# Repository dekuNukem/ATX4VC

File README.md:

# ATX4VC: ATX Power on Retro Computers!

[Buy ATX4VC](https://www.tindie.com/products/dekuNukem/atx4vc-atx-power-on-retro-computers/) | [Discord](https://discord.gg/T9uuFudg7j) | [User Manual](#user-manual) | [Table of Contents](#Table-of-Contents)

ATX4VC lets you **use ATX power supply on vintage computers**.

* Plug in ATX PSU on one end
* Get 12V, 5V, 3.3V, -12V, -5V out the other!

Features:

* All common voltage rails: +12V, +5V, +3.3V, -5V, -12V.
	* Also `5V Standby` and `Power-Good`
* Toolless Lever-Actuated Terminal Block
* USB-C Power Output
* 2x PC Fan Headers

You can use ATX4VC to:

* Replace retro computer PSUs
* Test and diagnose vintage hardware
* As general-purpose multi-voltage bench PSU

## Get ATX4VC

[Click me to get one!](https://www.tindie.com/products/dekuNukem/atx4vc-atx-power-on-retro-computers/)

## PicoRC

Also [check out PicoRC](https://picorc.com) for **device-specific** and **lower-cost** PicoPSU adaptors.

## Showcase

Here ATX4VC replaces the dead PSU in my IBM 5155 Portable PC, providing +12, +5, -12, and -5V.

Note the significant simplification and space/weight saving.

It also works as a **multi-voltage bench PSU** for testing and diagnostics.

Here it powers a Macintosh Plus motherboard with +12, +5, and -12V.

## Why

Power supplies are a major failure point of old computers today.

Those early PSUs are heavy, inefficient, and (slightly) explosive! After 40 odd years, many are not working, or worse might cause damage with out-of-spec voltages.

ATX4VC is designed to replace them with much more reliable modern ATX PSUs, and help test and diagnose vintage computers.

## User Manual

### ATX vs Pico PSU

ATX4VC works with **any ATX PSU**.

Although for **permanent retrofitting**, a **PicoPSU** is recommended due to its compact size.

* [Official website](https://www.mini-box.com/DC-DC) and [distributors](https://www.mini-box.com/site/resellers.html)
    * The cheapest **80W** one should be plenty for most
    * The **160W** variant is recommended if using many expansion cards and/or **spinning hard drive**
* Avoid **generic clones**
    * They over-rate and are of low quality
* A power brick with **12V DC** and **center positive** 5.5x2.5mm barrel jack is also needed.
    * They are very popular and you might already have one
    * Make sure it has enough wattage

### Quick Start

* Don't connect any load yet!

1. Plug in ATX connector
2. On **Power Mode** switch, select **Soft Power** (left position).
3. Press the button

PSU should turn on, voltage rail LEDs should light up. 

That's the gist of it! **Please do keep reading** for more info.

### Power Modes

* Soft Power
    * **Short press** once to turn on
    * Short press again to turn off
    * Suitable for **momentary push buttons**
* Hard Power
    * **Hold down** to power on
    * **Release** to power off
    * Suitable for **latching buttons / flip switches**
    * Connected directly to ATX **PS_ON** Signal

### External Power Button and Power LED

You can also attach an **external power button** and **power LED** to the headers below:

* Note LED polarity
* LED header has built-in **330 Ohm** resistor 
* Select suitable power mode
    * Soft Power: Momentary Pushbuttons
    * Hard Power: Latching Buttons / Flip Switches

### Power Connection

* See photo for power rails
    * For aux output harness, use **8P JST VH 3.96** female connector.
* 5VSB = 5V Standby
    * Available even when PSU is off
* Power Good Signal
    * 5V when all rails are stable
    * 0V otherwise

To connect a wire:

* Strip the insulation about 12mm / 0.5in.
* Lift handle, insert, push back down.

Also, make sure the conductor is thick enough!

Label the rails, vinyl stickers are available on the [product page](https://www.tindie.com/products/dekuNukem/atx4vc-atx-power-on-retro-computers/):

### Pre-flight Checks

Before powering up:

* Double check the **correct voltage terminal** is used
* Check for **dead shorts** between each voltage rail and GND, and between themselves!

Once powered up:

* Check voltage readings on each rail

Remember that ATX4VC **DOES NOT** monitor or condition voltage rails, so ensure the PSU itself is of good quality and trustworthy!

### Current Limit

* **`5 AMPS MAX`** OVER **ANY SINGLE RAIL**
* **`7 AMPS MAX`** **TOTAL CURRENT** OVER ALL RAILS

If more is needed, **tap the power directly** from a Molex connector.

See your PSU label or datasheet to see how much current it can provide:

### Fuses

* USE FUSES RATED **5A OR LESS**
* **DO NOT BYPASS FUSES**

ATX4VC uses common **automotive fuses**.

Regular, Mini, and Low-profile Mini all work.

Simply push into the holder.

### Fan Headers

Two PC Fan headers are available. You can plug in any regular **12V PC fan**, both 3-Pin and 4-Pin.

### USB-C Power Output

An USB-C port is available for **powering external devices**.

* **OUTPUT ONLY**, **DO NOT BACKFEED** with another powered device.

## Questions or Comments?

Feel free to ask in official [Discord Chatroom](https://discord.gg/T9uuFudg7j), raise a [Github issue](https://github.com/dekuNukem/ATX4VC/issues), or email `dekunukem` `gmail.com`!

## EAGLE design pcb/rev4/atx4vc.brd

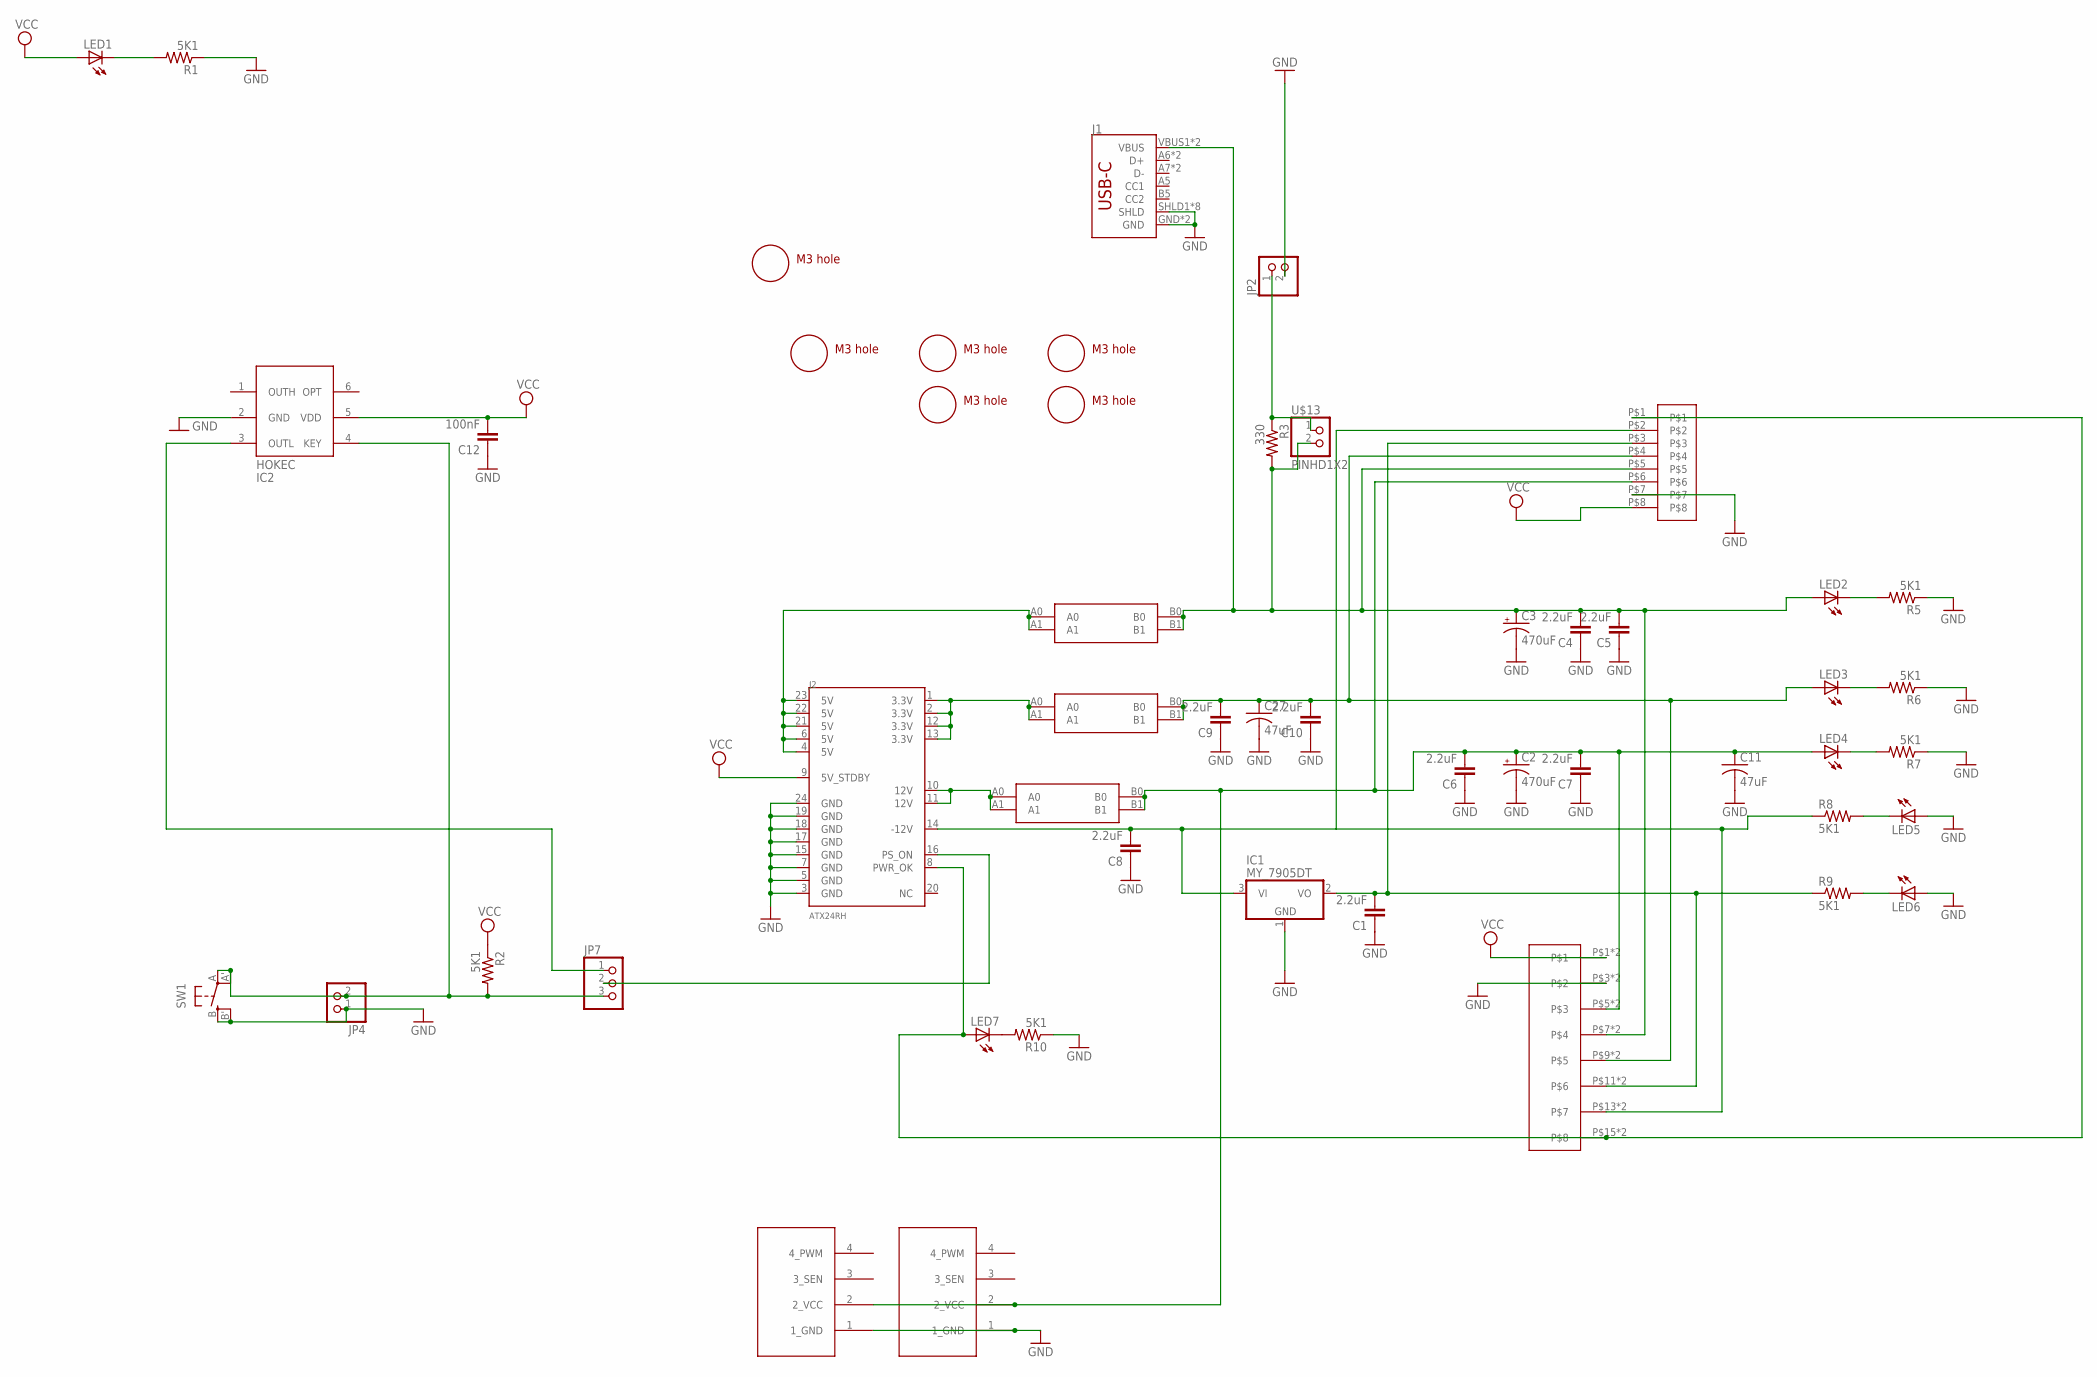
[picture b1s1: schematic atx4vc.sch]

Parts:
C1, C4, C5, C6, C7, C8, C9, C10: 2.2uF; 0805$1
C2, C3: 470uF; SMC_D
C11, C27: 47uF; C1210
C12: 100nF; 0805$1
IC1: MY_7905DT; ADAFRUIT_TO252
IC2: MAX486X/SOT; SOT23-6
J1: USB_C16PIN; USB-C-16P
J2: ATX24RH; ATX24_RIGHT_ANGLE
JP1, JP5: 4PIN_FAN; 1X04
JP2, JP4: PINHD-1X2; 1X02
JP7: PINHD-1X3CB; 1X03-CLEANBIG
LED1, LED2, LED3, LED4, LED5, LED6, LED7: LEDCHIP-LED0805; CHIP-LED0805
R1, R2, R5, R6, R7, R8, R9, R10: 5K1; 0805
R3: 330; 0805
SW1: SPST_TACT-EVQQ2; EVQ-Q2
U$1, U$2, U$3, U$4, U$5, U$6: M3_MOUNTING_HOLE; M3_MOUNTING_HOLE_PACK
U$7: 396_CONN_VH396_8P; 396_CONN_396_8P
U$9, U$10, U$11: CAR_FUSE_HOLDER3IN1; FUSE_HOLDER_3IN1
U$12: DG2204R-5.0-8DG2204-8; DG2204R-8
U$13: PINHD1X2; 1X02

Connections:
-5V: C1.2, IC1.2 (VO), R9.1, U$7.P$3, U$12.P$11, U$12.P$12
-12V: C8.2, IC1.3 (VI), J2.14 (-12V), R8.1, U$7.P$2, U$12.P$13, U$12.P$14
F3V3: C9.2, C10.2, C27.1, LED3.A, U$7.P$4, U$10.B0, U$10.B1, U$12.P$9, U$12.P$10
F5V: C3.+, C4.2, C5.2, J1.VBUS1 (VBUS), J1.VBUS2 (VBUS), LED2.A, R3.2, U$7.P$5, U$9.B0, U$9.B1, U$12.P$7, U$12.P$8, U$13.2
F12V: C2.+, C6.2, C7.2, C11.1, JP1.2 (2_VCC), JP5.2 (2_VCC), LED4.A, U$7.P$6, U$11.B0, U$11.B1, U$12.P$5, U$12.P$6
GND: C1.1, C2.-, C3.-, C4.1, C5.1, C6.1, C7.1, C8.1, C9.1, C10.1, C11.2, C12.1, C27.2, IC1.1 (GND), IC2.2 (GND), J1.GND, J1.GND2 (GND), J1.SHLD1 (SHLD), J1.SHLD2 (SHLD), J1.SHLD3 (SHLD), J1.SHLD4 (SHLD), J1.SHLD5 (SHLD), J1.SHLD6 (SHLD), J1.SHLD7 (SHLD), J1.SHLD8 (SHLD), J2.3 (GND), J2.5 (GND), J2.7 (GND), J2.15 (GND), J2.17 (GND), J2.18 (GND), J2.19 (GND), J2.24 (GND), JP1.1 (1_GND), JP2.2, JP4.1, JP5.1 (1_GND), LED5.A, LED6.A, R1.1, R5.1, R6.1, R7.1, R10.1, SW1.B (S), SW1.B' (S1), U$7.P$7, U$12.P$3, U$12.P$4
unnamed: LED7.C, R10.2
unnamed: LED6.C, R9.2
unnamed: IC2.3 (OUTL), JP7.1
unnamed: LED5.C, R8.2
unnamed: LED4.C, R7.2
unnamed: J2.4 (5V), J2.6 (5V), J2.21 (5V), J2.22 (5V), J2.23 (5V), U$9.A0, U$9.A1
unnamed: J2.8 (PWR_OK), LED7.A, U$7.P$1, U$12.P$15, U$12.P$16
unnamed: IC2.4 (KEY), JP4.2, JP7.3, R2.2, SW1.A, SW1.A' (P1)
unnamed: J2.1 (3.3V), J2.2 (3.3V), J2.12 (3.3V), J2.13 (3.3V), U$10.A0, U$10.A1
unnamed: J2.16 (PS_ON), JP7.2
unnamed: JP2.1, R3.1, U$13.1
unnamed: LED3.C, R6.2
unnamed: LED2.C, R5.2
unnamed: J2.10 (12V), J2.11 (12V), U$11.A0, U$11.A1
unnamed: LED1.C, R1.2
VCC: C12.2, IC2.5 (VDD), J2.9 (5V_STDBY), LED1.A, R2.1, U$7.P$8, U$12.P$1, U$12.P$2

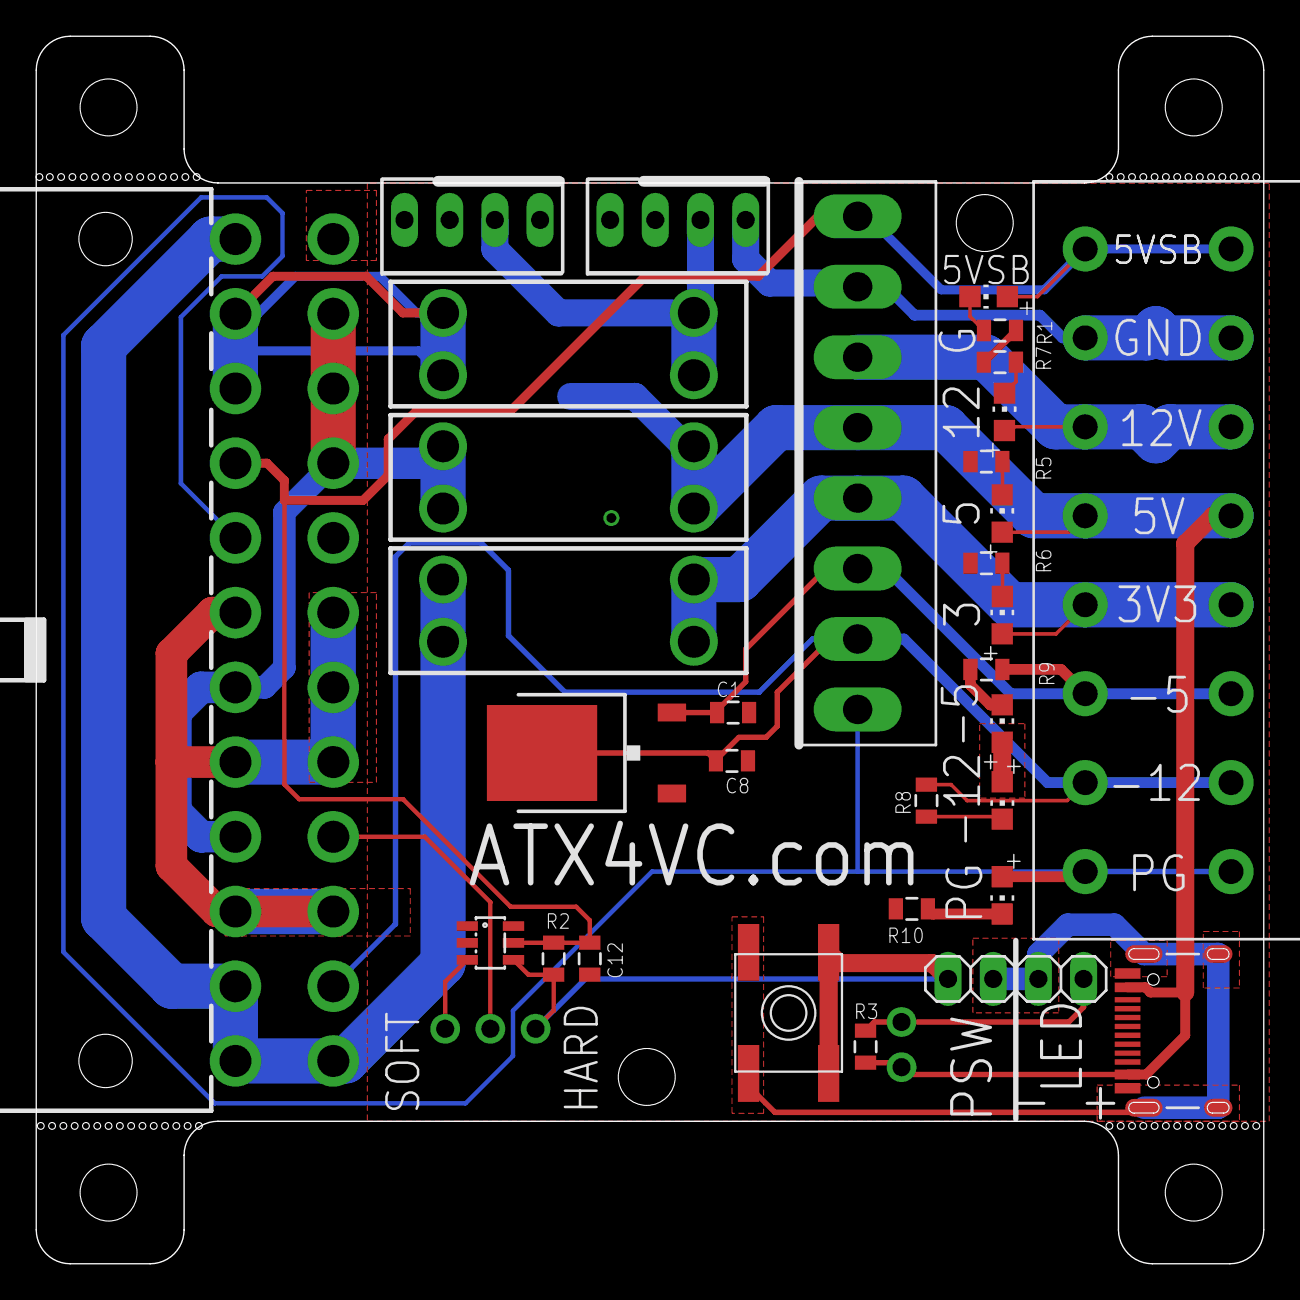
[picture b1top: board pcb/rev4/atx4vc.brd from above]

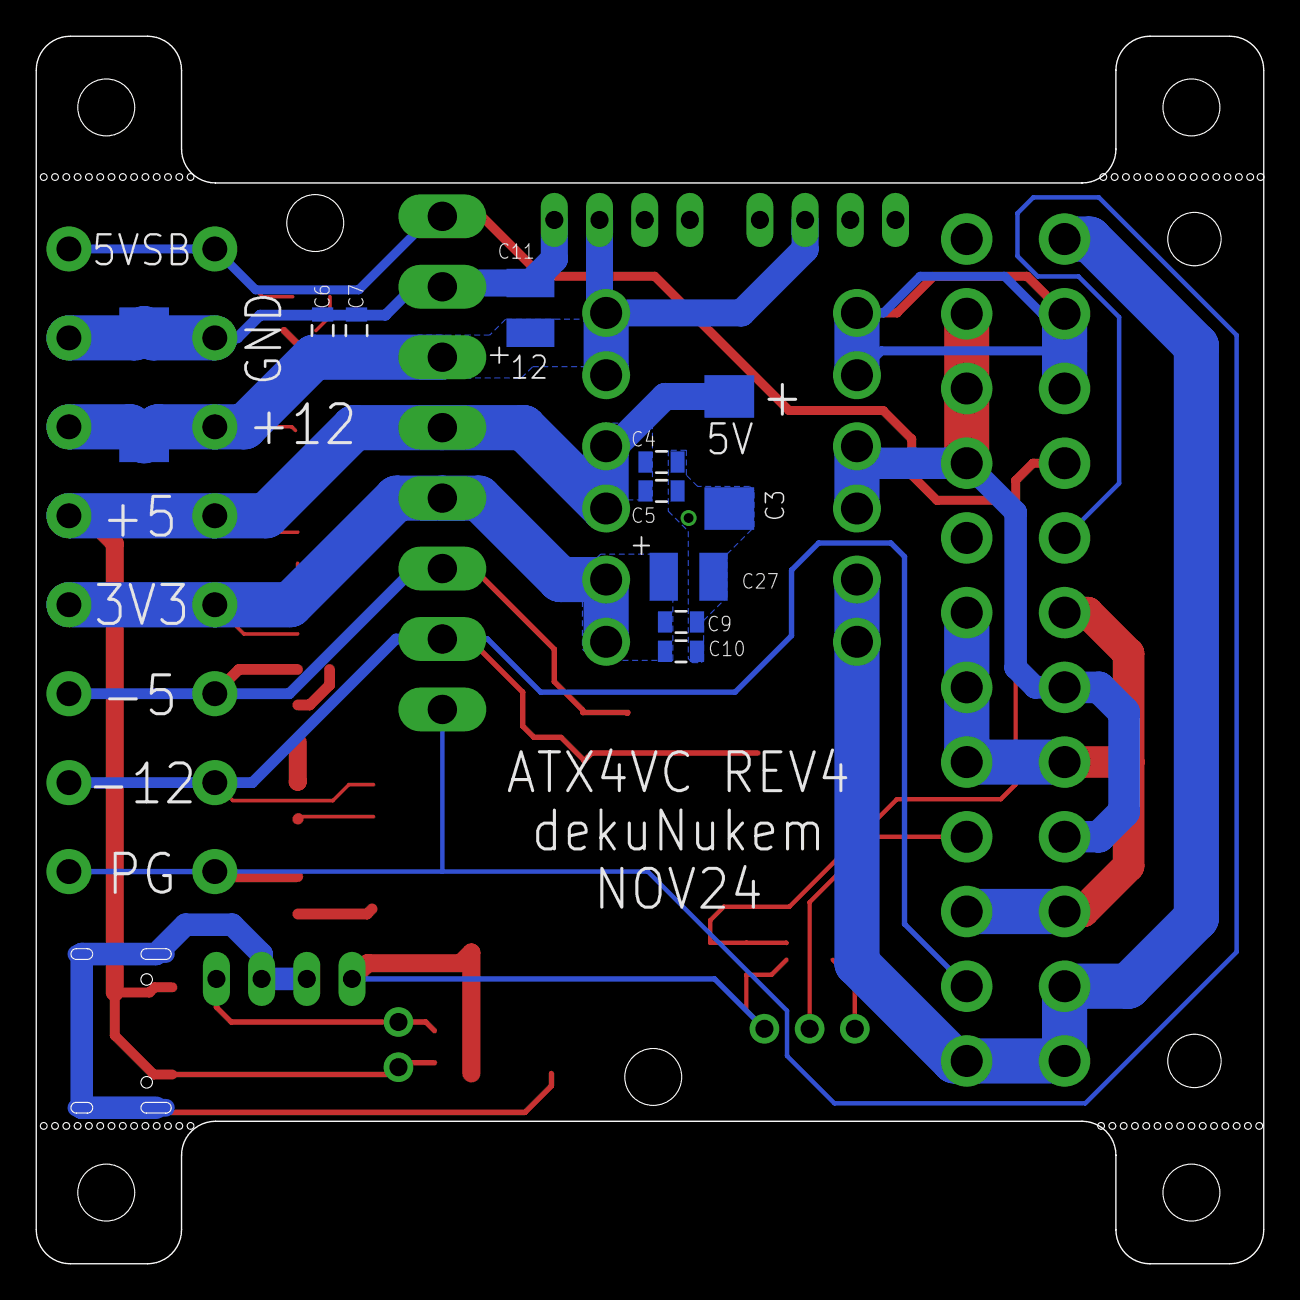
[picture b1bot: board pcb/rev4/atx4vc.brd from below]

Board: 2 copper layers, 69.0 x 69.0 mm, 51 parts (10 on the bottom side), 22 nets.

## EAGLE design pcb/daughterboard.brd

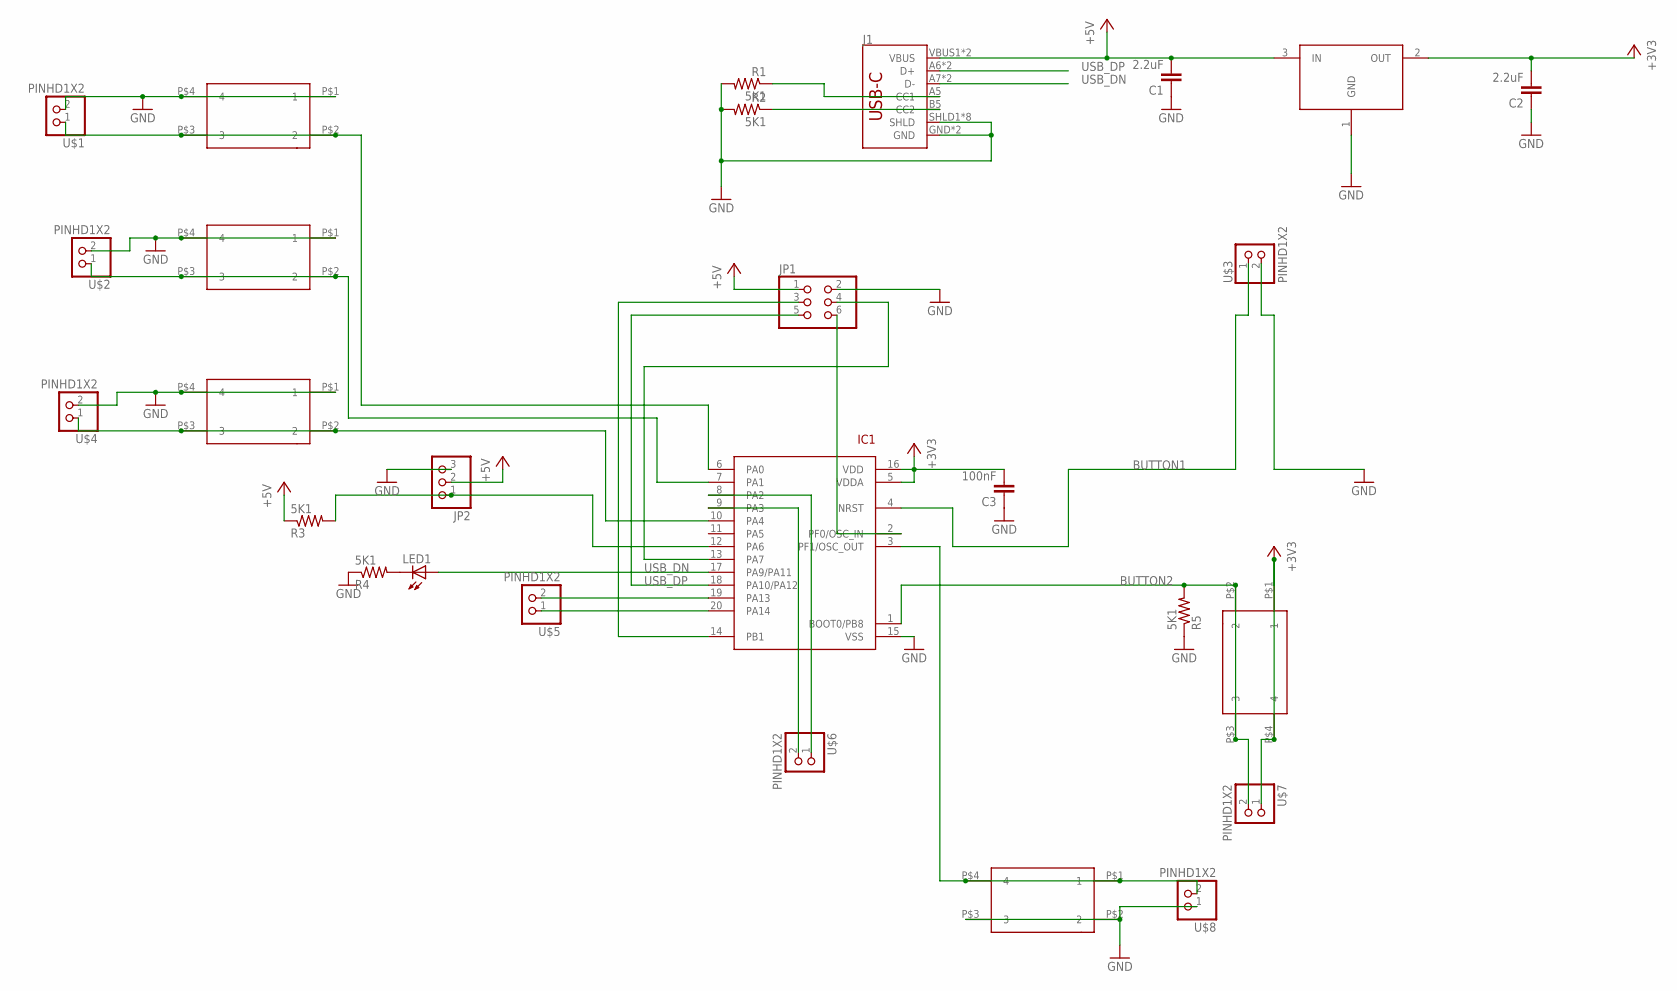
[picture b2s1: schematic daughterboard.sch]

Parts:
C1, C2: 2.2uF; 0805@1
C3: 100nF; 0805@1
IC1: STM32F042F4; TSSOP20
J1: USB_C16PIN; USB-C-16P
JP1: PINHD-2X3; 2X03
JP2: PINHD-1X3CB; 1X03-CLEANBIG
LED1: LEDCHIP-LED0805; CHIP-LED0805
R1, R2, R3, R4, R5: 5K1; 0805
SW1, SW2, SW3, SW4, SW5: 324_SW; 342_SWICH_FOOT
U1: XC6206_DEV; SOT23R_INFINEON
U$1, U$2, U$3, U$4, U$5, U$6, U$7, U$8: PINHD1X2; 1X02

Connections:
+3V3: C2.2, C3.2, IC1.5 (VDDA), IC1.16 (VDD), SW4.P$1 (1), SW4.P$4 (4), U1.2 (OUT), U$7.1
+5V: C1.2, J1.VBUS1 (VBUS), J1.VBUS2 (VBUS), JP1.1, JP2.2, R3.1, U1.3 (IN)
BUTTON1: IC1.4 (NRST), U$3.1
BUTTON2: IC1.1 (BOOT0/PB8), R5.2, SW4.P$2 (2), SW4.P$3 (3), U$7.2
GND: C1.1, C2.1, C3.1, IC1.15 (VSS), J1.GND, J1.GND2 (GND), J1.SHLD1 (SHLD), J1.SHLD2 (SHLD), J1.SHLD3 (SHLD), J1.SHLD4 (SHLD), J1.SHLD5 (SHLD), J1.SHLD6 (SHLD), J1.SHLD7 (SHLD), J1.SHLD8 (SHLD), JP1.2, JP2.3, R1.2, R2.2, R4.1, R5.1, SW1.P$1 (1), SW1.P$4 (4), SW2.P$1 (1), SW2.P$4 (4), SW3.P$1 (1), SW3.P$4 (4), SW5.P$2 (2), SW5.P$3 (3), U1.1 (GND), U$1.2, U$2.2, U$3.2, U$4.2, U$8.1
unnamed: IC1.13 (PA7), JP1.4
unnamed: IC1.14 (PB1), JP1.3
unnamed: IC1.19 (PA13), U$5.2
unnamed: IC1.20 (PA14), U$5.1
unnamed: IC1.12 (PA6), JP2.1, R3.2
unnamed: IC1.2 (PF0/OSC_IN), JP1.6
unnamed: IC1.8 (PA2), U$6.1
unnamed: IC1.9 (PA3), U$6.2
unnamed: IC1.10 (PA4), SW3.P$2 (2), SW3.P$3 (3), U$4.1
unnamed: IC1.7 (PA1), SW2.P$2 (2), SW2.P$3 (3), U$2.1
unnamed: IC1.6 (PA0), SW1.P$2 (2), SW1.P$3 (3), U$1.1
unnamed: IC1.3 (PF1/OSC_OUT), SW5.P$1 (1), SW5.P$4 (4), U$8.2
unnamed: LED1.C, R4.2
unnamed: J1.B5 (CC2), R2.1
unnamed: J1.A5 (CC1), R1.1
USB_DN: IC1.17 (PA9/PA11), J1.A7 (D-), J1.B7 (D-), LED1.A
USB_DP: IC1.18 (PA10/PA12), J1.A6 (D+), J1.B6 (D+), JP1.5

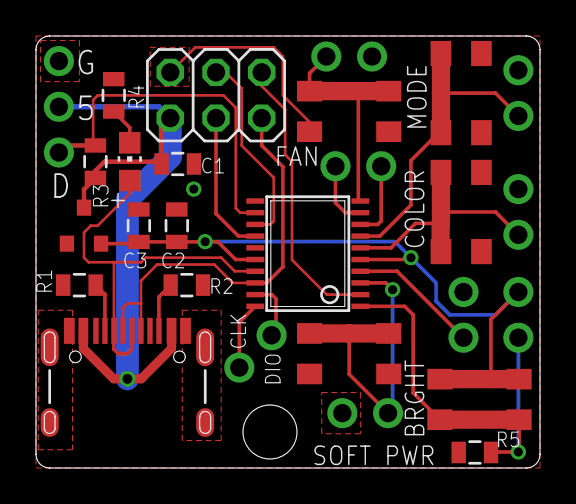
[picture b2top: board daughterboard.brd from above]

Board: 2 copper layers, 28.0 x 24.0 mm, 27 parts (0 on the bottom side), 22 nets.

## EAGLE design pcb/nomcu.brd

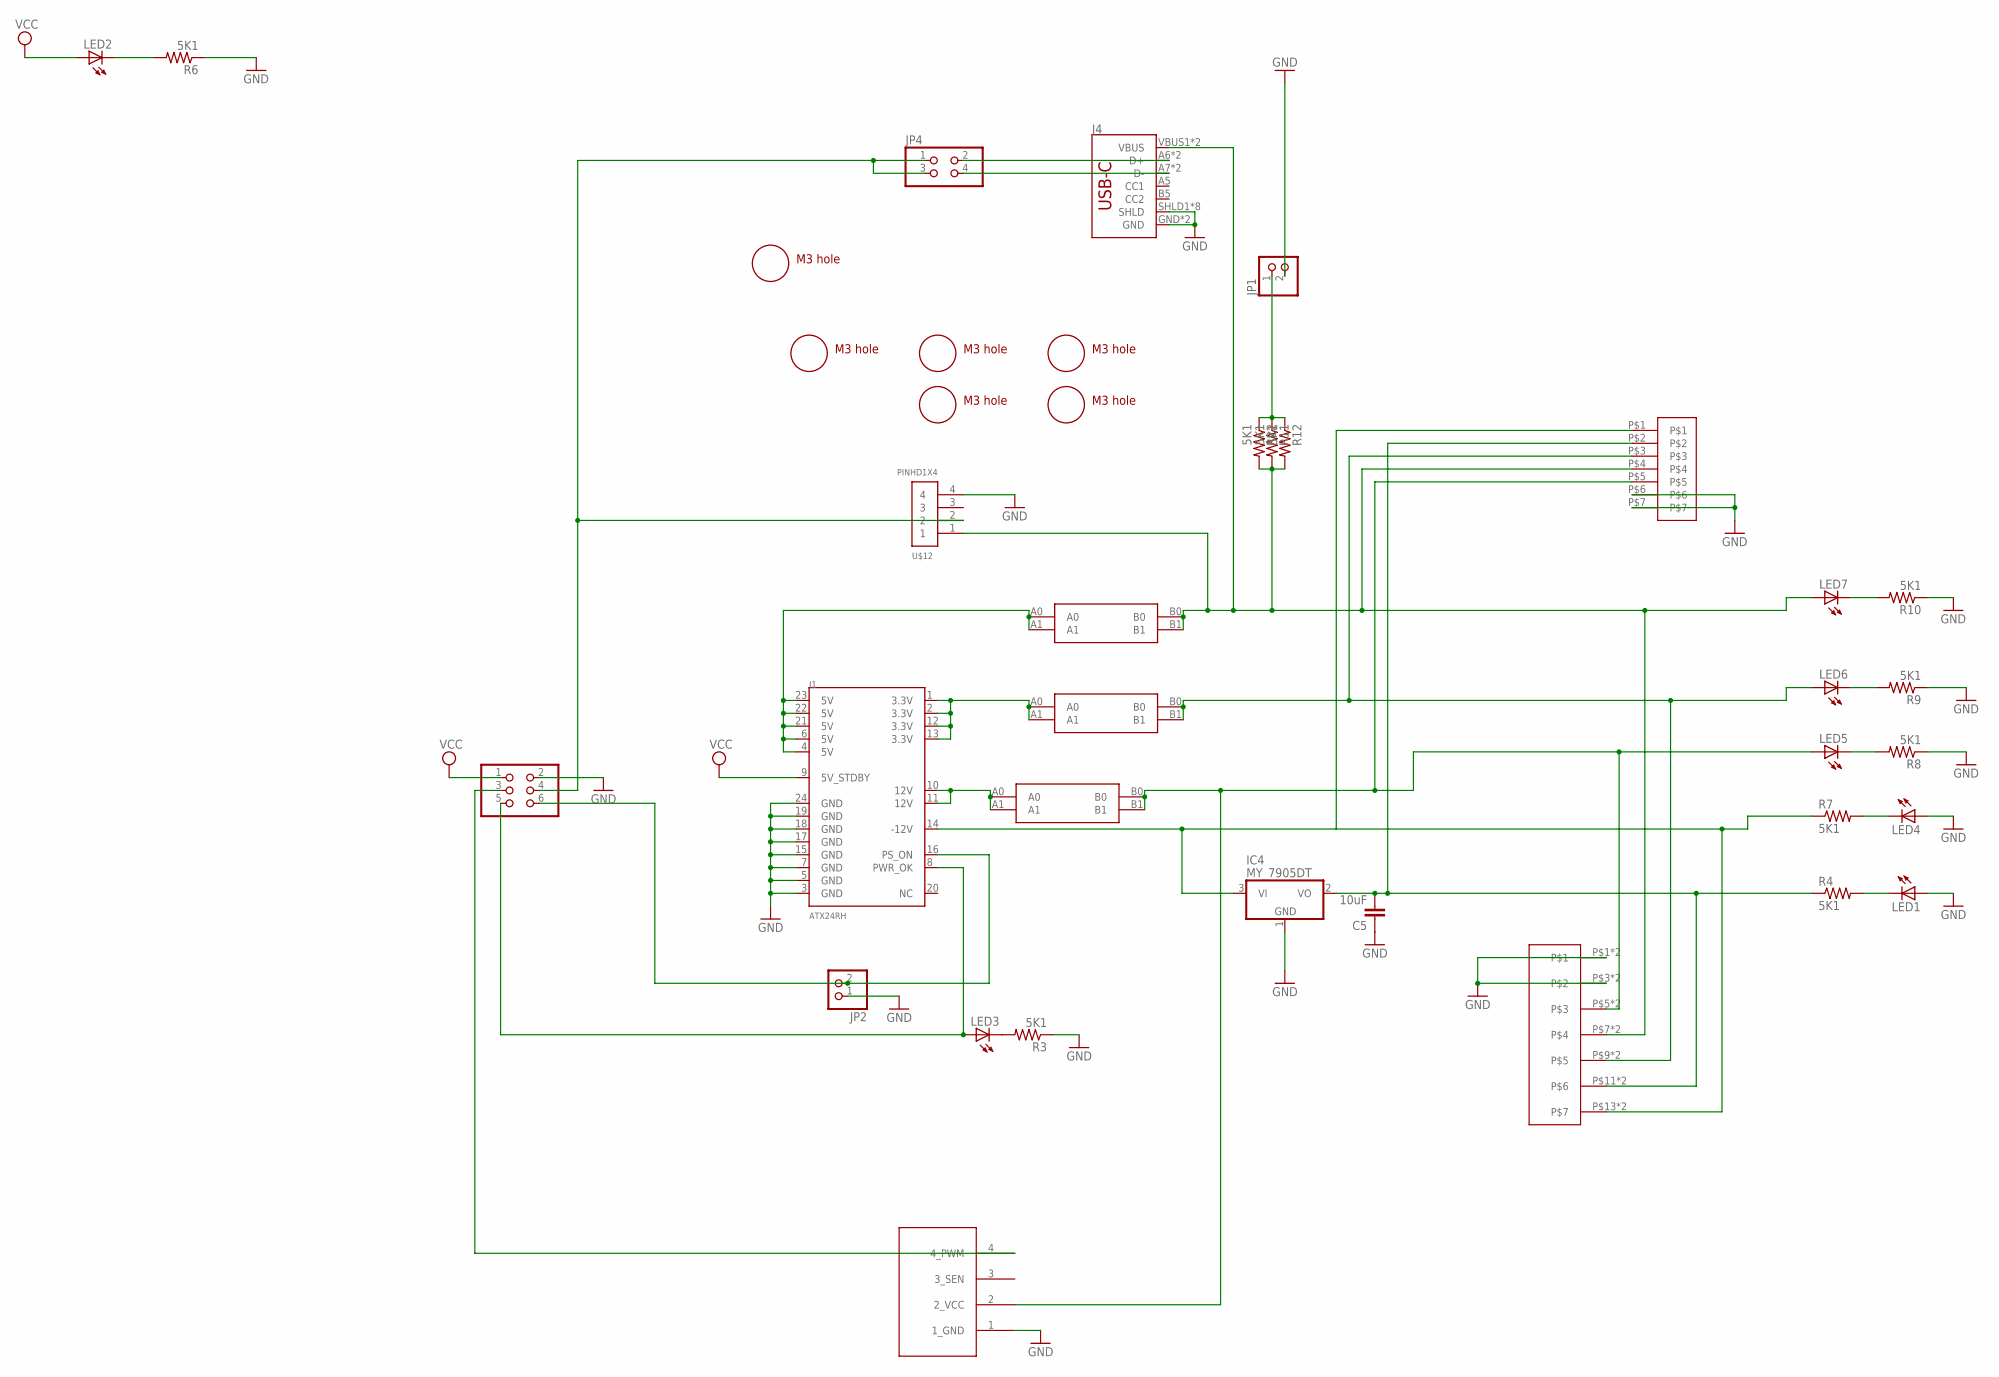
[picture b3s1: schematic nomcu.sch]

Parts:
C5: 10uF; 0805$1
IC4: MY_7905DT; ADAFRUIT_TO252
J1: ATX24RH; ATX24_RIGHT_ANGLE
J4: USB_C16PIN; USB-C-16P
JP1, JP2: PINHD-1X2; 1X02
JP3: PINHD-2X3; 2X03
JP4: PINHD-2X2; 2X02
JP8: 4PIN_FAN; 1X04
LED1, LED2, LED3, LED4, LED5, LED6, LED7: LEDCHIP-LED0805; CHIP-LED0805
R3, R4, R6, R7, R8, R9, R10, R11, R12, R22: 5K1; 0805
U$1, U$2, U$3, U$6, U$10, U$11: M3_MOUNTING_HOLE; M3_MOUNTING_HOLE_PACK
U$4: VH396; 396_7P
U$5, U$7, U$8: CAR_FUSE_HOLDER3IN1; FUSE_HOLDER_3IN1
U$9: DG2204R-5.0; DG2204R
U$12: PINHD1X4; 1X04-CLEANBIG

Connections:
-5V: C5.2, IC4.2 (VO), R4.1, U$4.P$2, U$9.P$11, U$9.P$12
-12V: IC4.3 (VI), J1.14 (-12V), R7.1, U$4.P$1, U$9.P$13, U$9.P$14
F3V3: LED6.A, U$4.P$3, U$7.B0, U$7.B1, U$9.P$9, U$9.P$10
F5V: J4.VBUS1 (VBUS), J4.VBUS2 (VBUS), LED7.A, R11.2, R12.2, R22.2, U$4.P$4, U$8.B0, U$8.B1, U$9.P$7, U$9.P$8, U$12.1
F12V: JP8.2 (2_VCC), LED5.A, U$4.P$5, U$5.B0, U$5.B1, U$9.P$5, U$9.P$6
GND: C5.1, IC4.1 (GND), J1.3 (GND), J1.5 (GND), J1.7 (GND), J1.15 (GND), J1.17 (GND), J1.18 (GND), J1.19 (GND), J1.24 (GND), J4.GND, J4.GND2 (GND), J4.SHLD1 (SHLD), J4.SHLD2 (SHLD), J4.SHLD3 (SHLD), J4.SHLD4 (SHLD), J4.SHLD5 (SHLD), J4.SHLD6 (SHLD), J4.SHLD7 (SHLD), J4.SHLD8 (SHLD), JP1.2, JP2.1, JP3.2, JP8.1 (1_GND), LED1.A, LED4.A, R3.1, R6.1, R8.1, R9.1, R10.1, U$4.P$6, U$4.P$7, U$9.P$1, U$9.P$2, U$9.P$3, U$9.P$4, U$12.4
unnamed: LED3.C, R3.2
unnamed: JP3.3, JP8.4 (4_PWM)
unnamed: J4.A6 (D+), J4.B6 (D+), JP4.2
unnamed: LED1.C, R4.2
unnamed: J4.A7 (D-), J4.B7 (D-), JP4.4
unnamed: JP3.4, JP4.1, JP4.3, U$12.2
unnamed: LED4.C, R7.2
unnamed: LED5.C, R8.2
unnamed: J1.4 (5V), J1.6 (5V), J1.21 (5V), J1.22 (5V), J1.23 (5V), U$8.A0, U$8.A1
unnamed: J1.8 (PWR_OK), JP3.5, LED3.A
unnamed: J1.1 (3.3V), J1.2 (3.3V), J1.12 (3.3V), J1.13 (3.3V), U$7.A0, U$7.A1
unnamed: J1.16 (PS_ON), JP2.2, JP3.6
unnamed: JP1.1, R11.1, R12.1, R22.1
unnamed: LED6.C, R9.2
unnamed: LED7.C, R10.2
unnamed: J1.10 (12V), J1.11 (12V), U$5.A0, U$5.A1
unnamed: LED2.C, R6.2
VCC: J1.9 (5V_STDBY), JP3.1, LED2.A

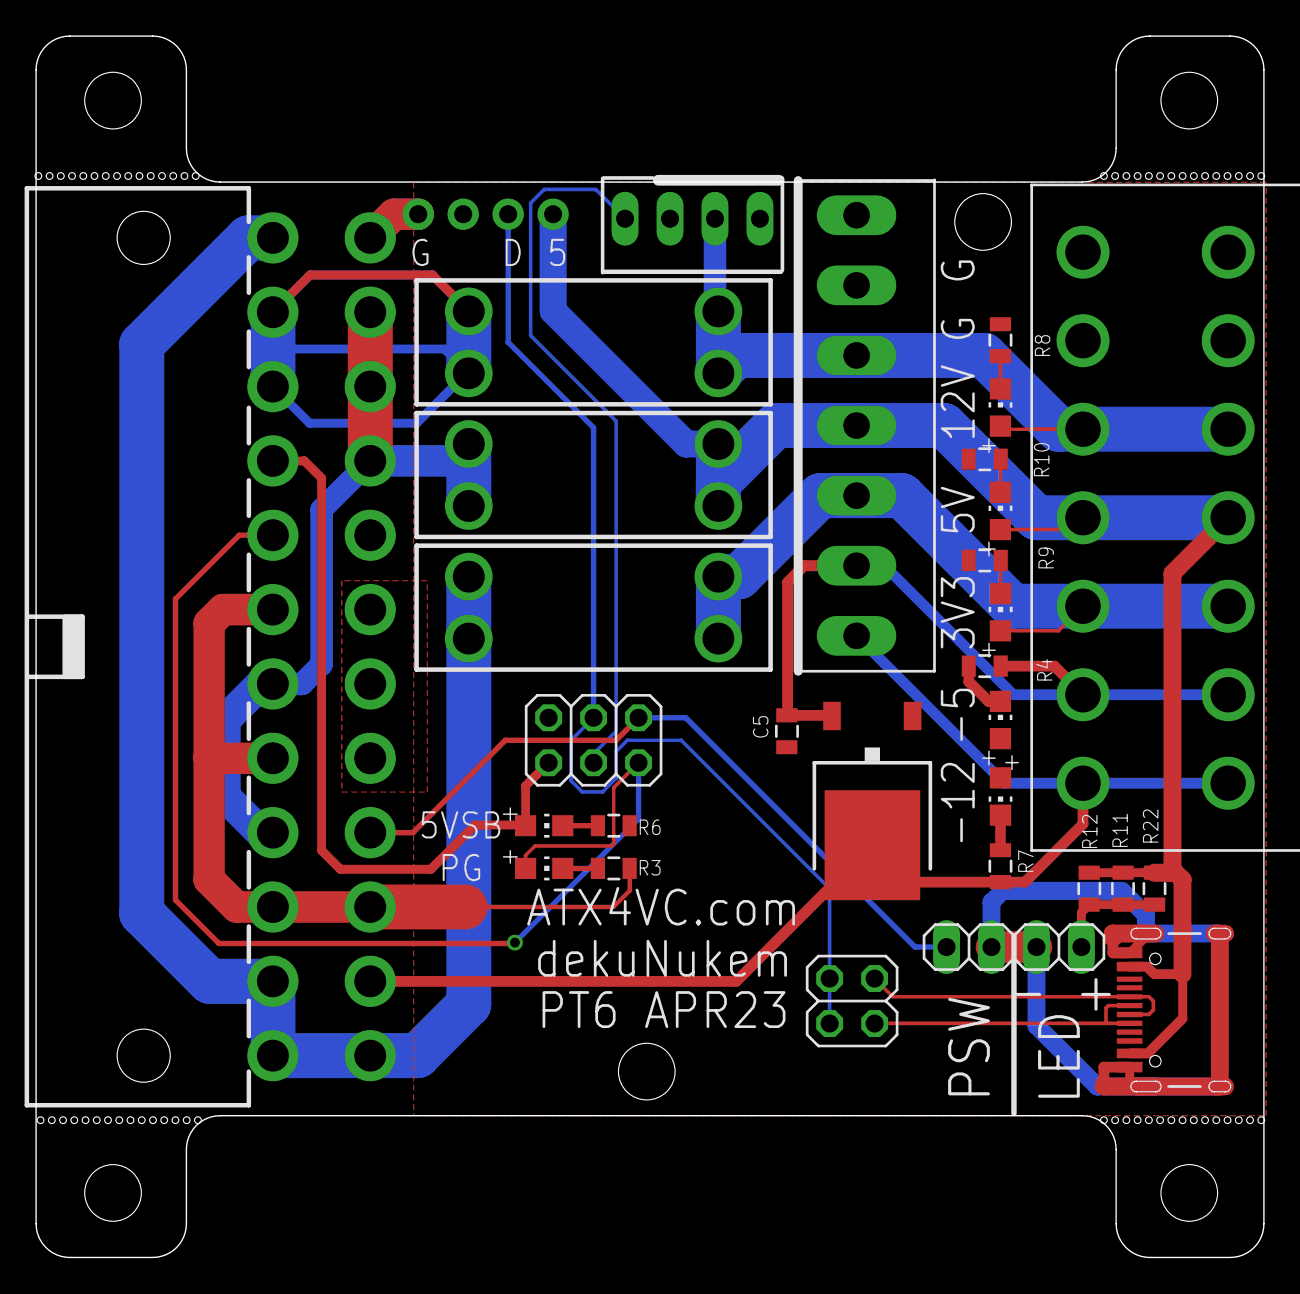
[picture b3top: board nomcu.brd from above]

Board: 2 copper layers, 69.4 x 69.0 mm, 38 parts (0 on the bottom side), 24 nets.

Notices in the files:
parts and their libraries:
SparkFun-Passives: Licensing: Creative Commons ShareAlike 4.0 International - https://creativecommons.org/licenses/by-sa/4.0
